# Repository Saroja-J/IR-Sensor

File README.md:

# 📡 IR Sensor using LM358 Comparator

A simple **Infrared (IR) Sensor** designed in **KiCad** using the **LM358 operational amplifier** as a comparator. The circuit detects nearby objects by transmitting infrared light and sensing its reflection. The received signal is compared with a reference voltage, and when an object is detected, the output changes state and the indicator LED turns ON. The detection sensitivity can be adjusted using a potentiometer, making the circuit suitable for applications such as obstacle detection, object counting, line-following robots, and automation projects.

---

## 📖 Overview

This project consists of an **IR LED** that continuously emits infrared light and a **photodiode** that receives the reflected IR light from nearby objects. The **LM358 Op-Amp** compares the photodiode's output with a reference voltage set by the potentiometer. If the reflected IR light is strong enough, the comparator output becomes HIGH, turning ON the output LED and providing a digital output signal. The adjustable potentiometer allows the sensing distance to be tuned according to the application.

---

## 📷 PCB Design

---

## ⚙️ How It Works

1. A **5V DC** supply powers the circuit.
2. The IR LED emits infrared light continuously.
3. When an object comes near, the IR light is reflected back to the photodiode.
4. The photodiode converts the reflected light into a voltage.
5. The LM358 compares this voltage with the reference voltage.
6. If the reflected signal exceeds the set threshold, the output goes HIGH and the LED turns ON.

---

## ✨ Features

- ✔️ Infrared object detection
- ✔️ Adjustable sensing sensitivity
- ✔️ LM358 used as a comparator
- ✔️ LED indication for object detection
- ✔️ Simple and low-cost design
- ✔️ Designed using KiCad

---

## 🛠️ Components

| Component | Description |
|-----------|-------------|
| LM358 Op-Amp | Compares the sensor signal with the reference voltage and generates the output. |
| IR LED | Emits infrared light for object detection. |
| Photodiode | Detects the reflected infrared light from nearby objects. |
| Potentiometer (RV1) | Adjusts the sensing sensitivity. |
| Resistors (R1, R2, R3) | Limit current and help set the operating conditions of the circuit. |
| LED | Indicates when an object is detected. |
| 5V DC Supply | Powers the entire circuit. |
| Output Connector | Provides the digital output signal. |

---

## 📄 License

This project is intended for **educational and learning purposes**.
```

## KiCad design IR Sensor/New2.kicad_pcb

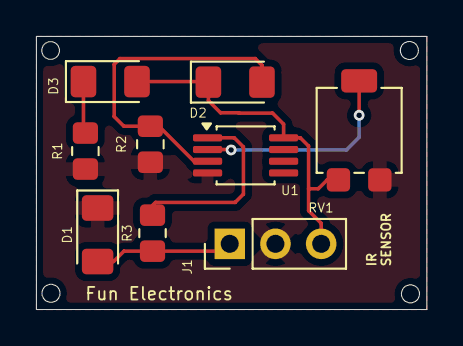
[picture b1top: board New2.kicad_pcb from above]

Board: 2 copper layers, 21.7 x 15.2 mm, 9 parts (0 on the bottom side), 7 nets.

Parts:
D1: LED; LED_1206_3216Metric_Pad1.42x1.75mm_HandSolder
D2: D_Photo; D_1206_3216Metric_Pad1.42x1.75mm_HandSolder
D3: IR26-21C_L110_TR8; LED_1206_3216Metric_Pad1.42x1.75mm_HandSolder
J1: Conn_01x03_Pin; PinHeader_1x03_P2.54mm_Vertical
R1, R2, R3: R_US; R_0805_2012Metric_Pad1.20x1.40mm_HandSolder
RV1: R_Potentiometer_US; Potentiometer_Bourns_3314G_Vertical
U1: LM358; MSOP-8_3x3mm_P0.65mm

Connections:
+5V: D2.1 (K), D3.2 (A), J1.3, RV1.1, U1.8 (V+)
/o/p: D1.2 (A), J1.1, R3.2
GND: D1.1 (K), J1.2, R1.2, R2.2, RV1.3, U1.4 (V-)
unnamed: D2.2 (A), R2.1, U1.3 (+)
unnamed: D3.1 (K), R1.1
unnamed: R3.1, U1.1
unnamed: RV1.2, U1.2 (-)
